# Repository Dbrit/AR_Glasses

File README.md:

# The HUDset
EE445L AR glasses final project

https://www.youtube.com/watch?v=10rfZ0_9bQ0

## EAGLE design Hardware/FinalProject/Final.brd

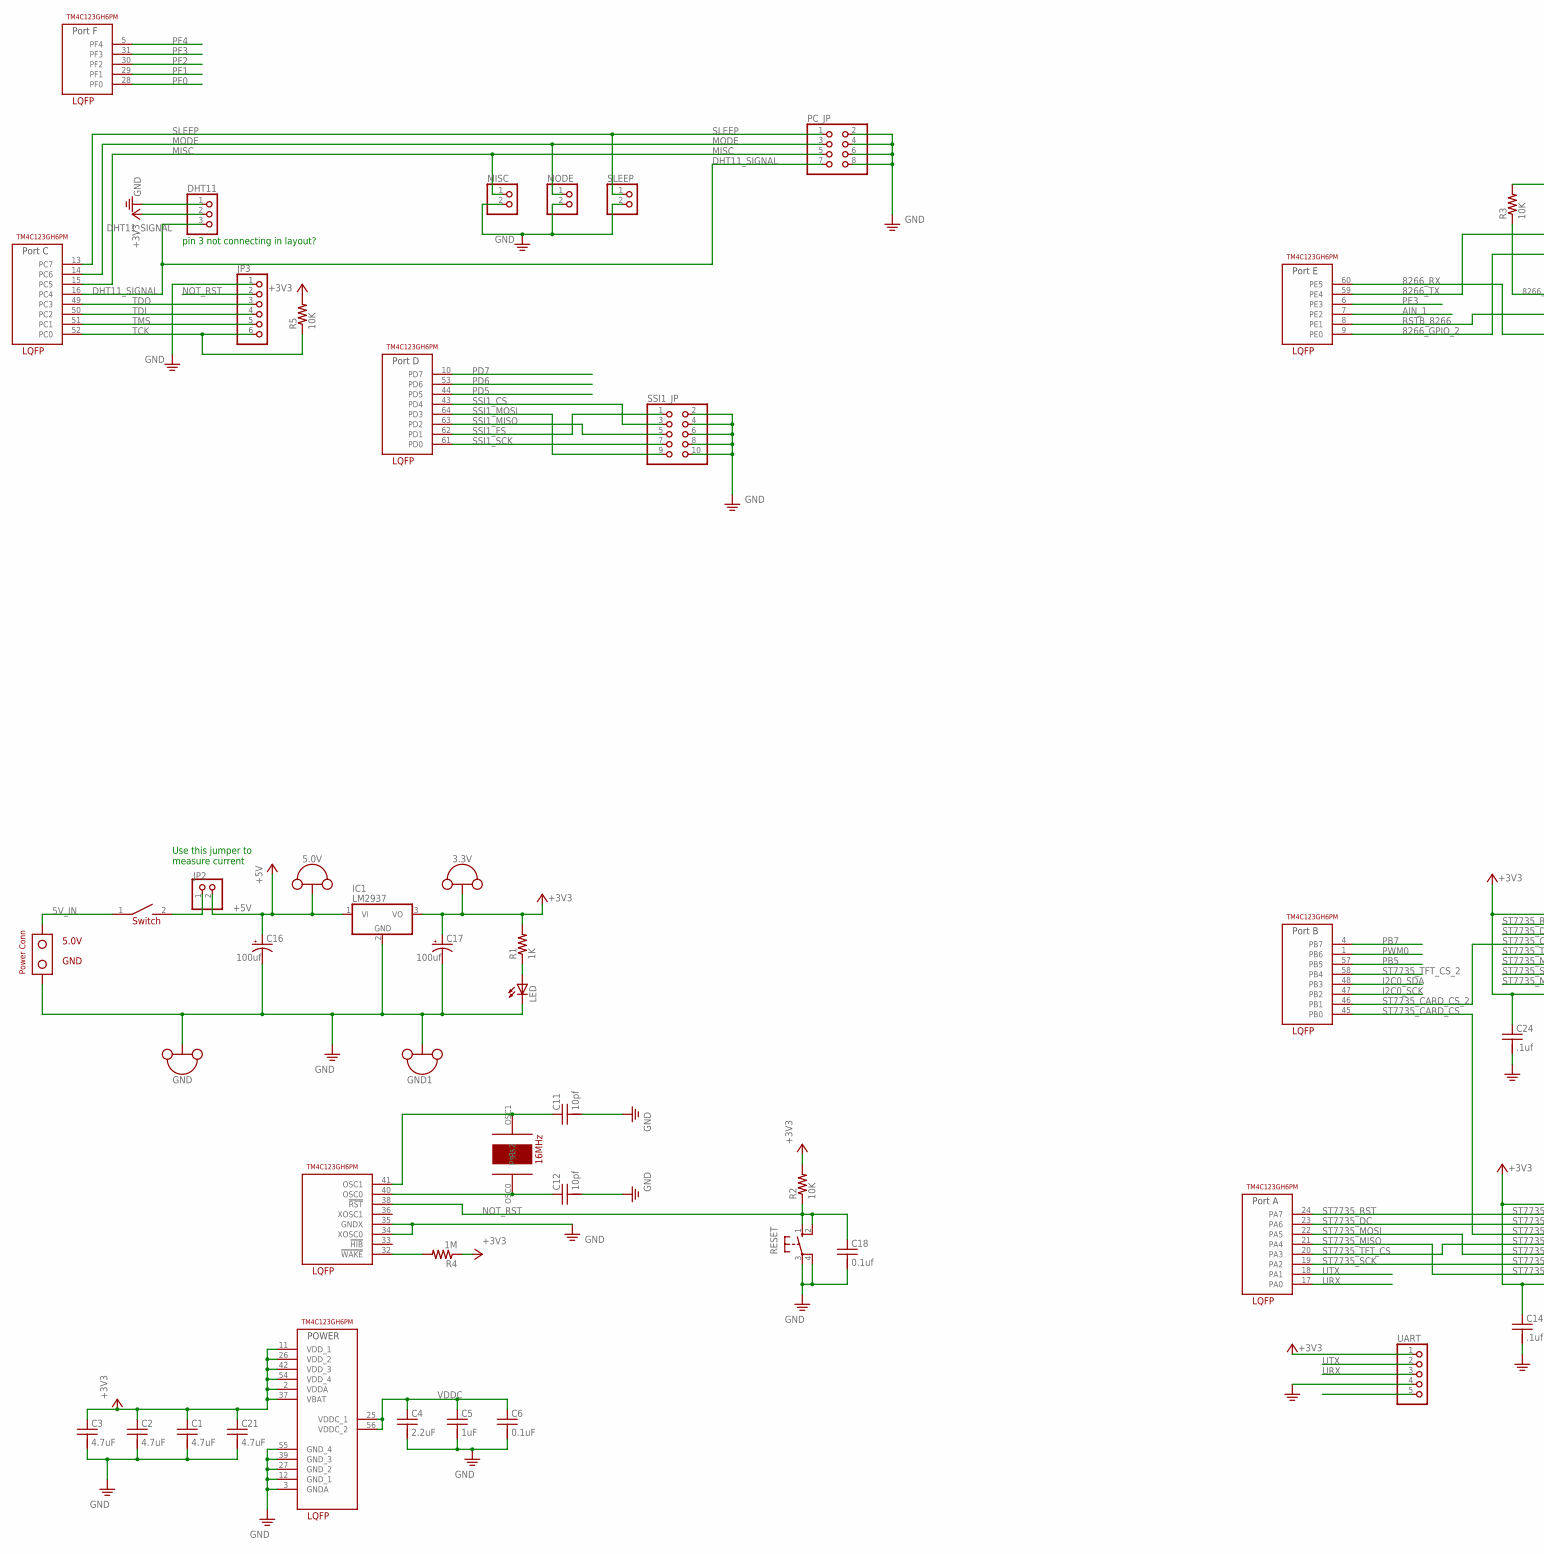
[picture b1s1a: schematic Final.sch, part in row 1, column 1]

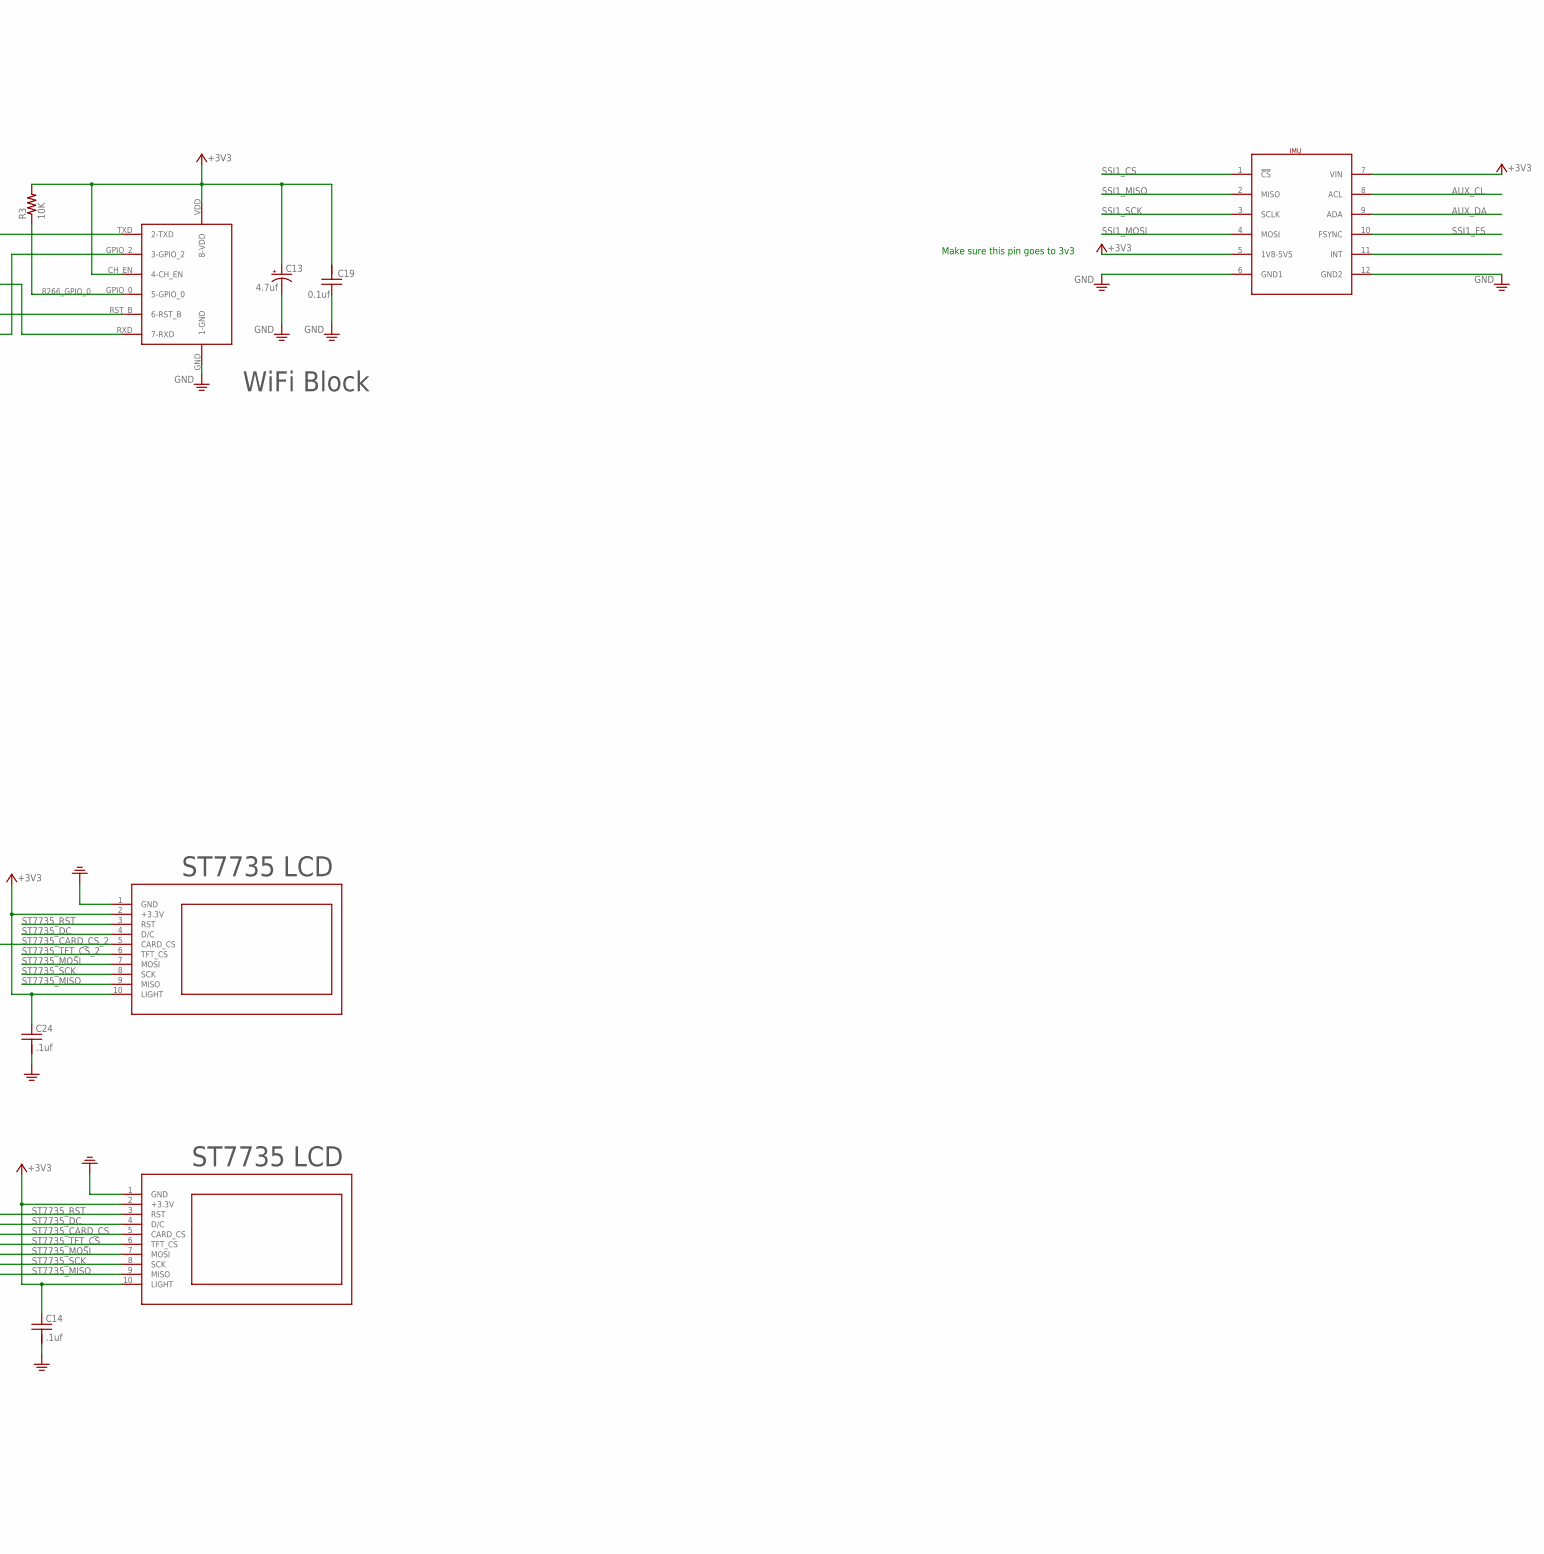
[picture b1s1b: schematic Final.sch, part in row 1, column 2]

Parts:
3.3V, 5.0V: TP_LOOP
C1, C2, C3, C21: 4.7uF; C0603K
C4: 2.2uF; C0603K
C5: 1uF; C0603K
C6: 0.1uF; C0603K
C11, C12: 10pf; CAP100MIL
C13: 4.7uf; CAP200MILPOLARIZED
C14, C24: .1uf; CAP200MIL
C16, C17: 100uf; CAP200MILPOLARIZED
C18: 0.1uf; CAP100MIL
C19: 0.1uf; CAP200MIL
DHT11: PINHD-1X3; 1X03
GND, GND1: TP_LOOP
IC1: LM2937; TO220
IMU: SEN-15335
JP2: PINHD-1X2; 1X02
JP3: PINHD-1X6; 1X06
LED: LED5MM
MISC: PINHD-1X2; 1X02
MODE: PINHD-1X2; 1X02
PC_JP: PINHD-2X4; 2X04
POWER_SWITCH: SW_POWER_100MIL; SW_POWER
R1: 1K; RES200MIL
R2, R5: 10K; RES200MIL
R3: 10K; RES300MIL
R4: 1M; RES200MIL
RESET: B3F-1052; B3F-10XX
SLEEP: PINHD-1X2; 1X02
SSI1_JP: PINHD-2X5; 2X05
U$1: TM4C123GH6PM; QFP50P1200X1200X160-64N
U$2: 16MHZ_CRYSTAL
U$3: ESP_8266; ESP8266
U$4: POWER_CONN
U$5, U$6: ST7735
UART: PINHD-1X5; 1X05

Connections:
5V_IN: POWER_SWITCH.1, U$4.VDD
8266_GPIO_0: R3.1, U$3.GPIO_0 (5-GPIO_0)
8266_GPIO_2: U$1.9 (PE0), U$3.GPIO_2 (3-GPIO_2)
8266_RX: U$1.60 (PE5), U$3.RXD (7-RXD)
8266_TX: U$1.59 (PE4), U$3.TXD (2-TXD)
+3V3: 3.3V.P$1, 3.3V.P$2, C1.1, C2.1, C3.1, C13.+, C14.1, C17.+, C19.2, C21.1, C24.1, DHT11.2, IC1.3 (VO), IMU.5 (1V8-5V5), IMU.7 (VIN), R1.2, R2.2, R3.2, R4.1, R5.2, U$1.2 (VDDA), U$1.11 (VDD_1), U$1.26 (VDD_2), U$1.37 (VBAT), U$1.42 (VDD_3), U$1.54 (VDD_4), U$3.CH_EN (4-CH_EN), U$3.VDD (8-VDD), U$5.2 (+3.3V), U$5.10 (LIGHT), U$6.2 (+3.3V), U$6.10 (LIGHT), UART.1
+5V: 5.0V.P$1, 5.0V.P$2, C16.+, IC1.1 (VI), JP2.2
AIN_1: U$1.7 (PE2)
AUX_CL: IMU.8 (ACL)
AUX_DA: IMU.9 (ADA)
CURRENT_1: JP2.1, POWER_SWITCH.2
DHT11_SIGNAL: DHT11.3, PC_JP.7, U$1.16 (PC4)
GND: C1.2, C2.2, C3.2, C4.2, C5.2, C6.2, C11.2, C12.2, C13.-, C14.2, C16.-, C17.-, C18.2, C19.1, C21.2, C24.2, DHT11.1, GND.P$1, GND.P$2, GND1.P$1, GND1.P$2, IC1.2 (GND), IMU.6 (GND1), IMU.12 (GND2), JP3.1, LED.K (C), MISC.2, MODE.2, PC_JP.2, PC_JP.4, PC_JP.6, PC_JP.8, RESET.3, RESET.4 (P1), SLEEP.2, SSI1_JP.2, SSI1_JP.4, SSI1_JP.6, SSI1_JP.8, SSI1_JP.10, U$1.3 (GNDA), U$1.12 (GND_1), U$1.27 (GND_2), U$1.34 (XOSC0), U$1.35 (GNDX), U$1.39 (GND_3), U$1.55 (GND_4), U$3.GND (1-GND), U$4.GND, U$5.1 (GND), U$6.1 (GND), UART.4
I2C0_SCK: U$1.47 (PB2)
I2C0_SDA: U$1.48 (PB3)
LED_CATHODE: LED.A, R1.1
MISC: MISC.1, PC_JP.5, U$1.15 (PC5)
MODE: MODE.1, PC_JP.3, U$1.14 (PC6)
NOT_RST: C18.1, JP3.2, R2.1, RESET.1 (S), RESET.2 (S1), U$1.38 (!RST)
NOT_WAKE: R4.2, U$1.32 (!WAKE)
OSC0: C12.1, U$1.40 (OSC0), U$2.OSC0
OSC1: C11.1, U$1.41 (OSC1), U$2.OSC1
PB5: U$1.57 (PB5)
PB7: U$1.4 (PB7)
PD5: U$1.44 (PD5)
PD6: U$1.53 (PD6)
PD7: U$1.10 (PD7)
PE3: U$1.6 (PE3)
PF0: U$1.28 (PF0)
PF1: U$1.29 (PF1)
PF2: U$1.30 (PF2)
PF3: U$1.31 (PF3)
PF4: U$1.5 (PF4)
PWM0: U$1.1 (PB6)
RSTB_8266: U$1.8 (PE1), U$3.RST_B (6-RST_B)
SLEEP: PC_JP.1, SLEEP.1, U$1.13 (PC7)
SSI1_CS: IMU.1 (!CS), SSI1_JP.3, U$1.43 (PD4)
SSI1_FS: IMU.10 (FSYNC), SSI1_JP.1, U$1.62 (PD1)
SSI1_MISO: IMU.2 (MISO), SSI1_JP.5, U$1.63 (PD2)
SSI1_MOSI: IMU.4 (MOSI), SSI1_JP.9, U$1.64 (PD3)
SSI1_SCK: IMU.3 (SCLK), SSI1_JP.7, U$1.61 (PD0)
ST7735_CARD_CS: U$1.45 (PB0), U$5.5 (CARD_CS)
ST7735_CARD_CS_2: U$1.46 (PB1), U$6.5 (CARD_CS)
ST7735_DC: U$1.23 (PA6), U$5.4 (D/C), U$6.4 (D/C)
ST7735_MISO: U$1.21 (PA4), U$5.9 (MISO), U$6.9 (MISO)
ST7735_MOSI: U$1.22 (PA5), U$5.7 (MOSI), U$6.7 (MOSI)
ST7735_RST: U$1.24 (PA7), U$5.3 (RST), U$6.3 (RST)
ST7735_SCK: U$1.19 (PA2), U$5.8 (SCK), U$6.8 (SCK)
ST7735_TFT_CS: U$1.20 (PA3), U$5.6 (TFT_CS)
ST7735_TFT_CS_2: U$1.58 (PB4), U$6.6 (TFT_CS)
TCK: JP3.6, R5.1, U$1.52 (PC0)
TDI: JP3.4, U$1.50 (PC2)
TDO: JP3.3, U$1.49 (PC3)
TMS: JP3.5, U$1.51 (PC1)
URX: U$1.17 (PA0), UART.3
UTX: U$1.18 (PA1), UART.2
VDDC: C4.1, C5.1, C6.1, U$1.25 (VDDC_1), U$1.56 (VDDC_2)

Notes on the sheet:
WiFi Block
ST7735 LCD
Use this jumper to measure current
pin 3 not connecting in layout?
Make sure this pin goes to 3v3

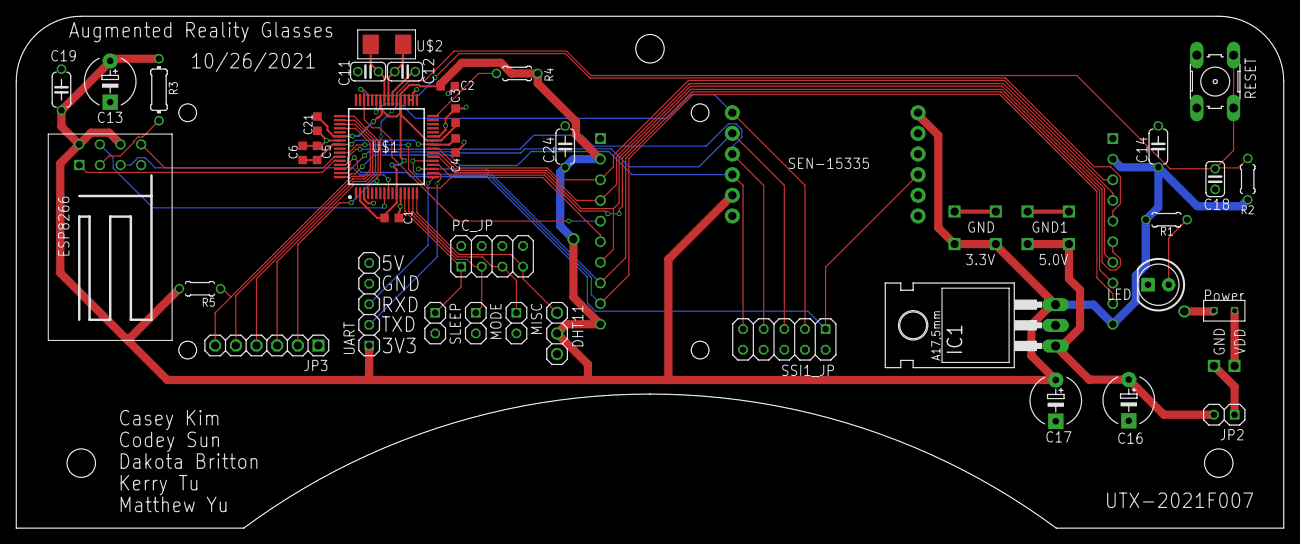
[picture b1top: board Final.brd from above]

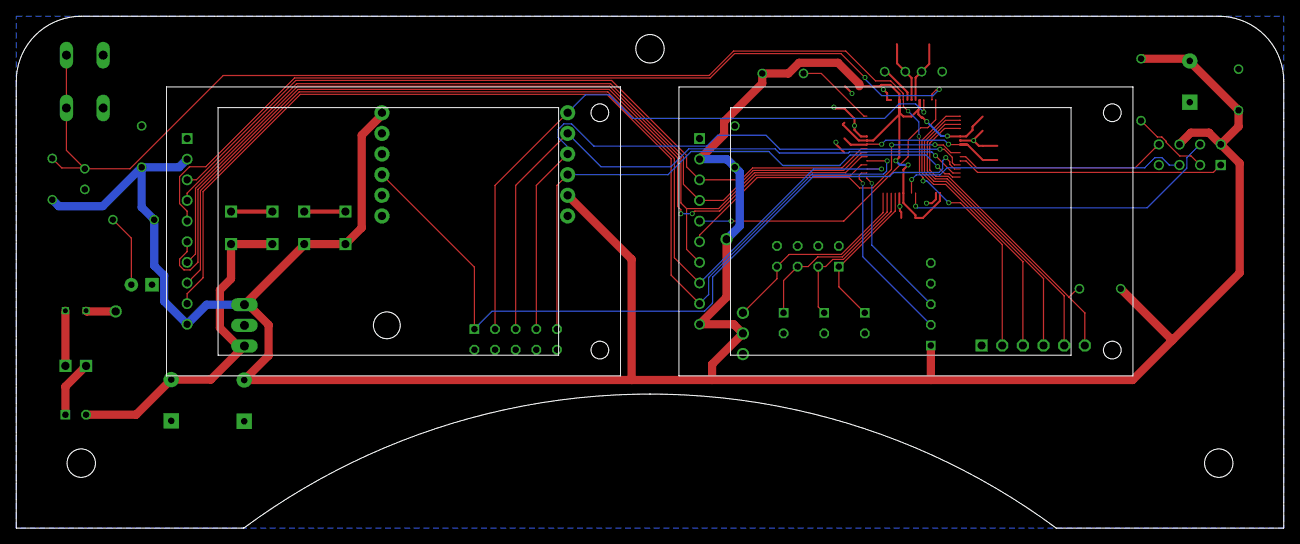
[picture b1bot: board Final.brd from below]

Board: 2 copper layers, 156.0 x 63.0 mm, 45 parts (2 on the bottom side), 40 nets.

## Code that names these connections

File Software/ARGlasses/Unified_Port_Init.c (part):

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// Port A drives the ST7735 LCD 
//
// Backlight (pin 10) connected to +3.3 V
// MISO      (pin 9)  connected to PA4
// SCK       (pin 8)  connected to PA2 (SSI0Clk)
// MOSI      (pin 7)  connected to PA5 (SSI0Tx)
// TFT_CS    (pin 6)  connected to PA3 (SSI0Fss)
// CARD_CS   (pin 5)  connected to PB0 (GPIO)
// Data/CMD  (pin 4)  connected to PA6 (GPIO), high for data, low for command
// RESET     (pin 3)  connected to PA7 (GPIO)
// VCC       (pin 2)  connected to +3.3 V
// Gnd       (pin 1)  connected to ground
//
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  SYSCTL_RCGCGPIO_R     |= 0x01;            // Activate port A
  while((SYSCTL_PRGPIO_R & 0x01)==0){};     // allow time for clock to start
    
  GPIO_PORTA_DIR_R      |= 0xC8;            // make PA3,6,7 out
  GPIO_PORTA_AFSEL_R    &= ~0xC8;           // disable alt funct on PA3,6,7
  GPIO_PORTA_DEN_R      |= 0xC8;            // enable digital I/O on PA3,6,7
  
  // configure PA3,6,7 as GPIO
  GPIO_PORTA_PCTL_R      = (GPIO_PORTA_PCTL_R
                         & 0x00FF0FFF)
                         + 0x00000000;
  
  GPIO_PORTA_AMSEL_R    &= ~0xC8;           // disable analog functionality on PA3,6,7

  // initialize SSI0
  GPIO_PORTA_AFSEL_R    |= 0x2C;            // enable alt funct on PA2,3,5
  GPIO_PORTA_DEN_R      |= 0x2C;            // enable digital I/O on PA2,3,5
 
  // configure PA2,3,5 as SSI
  GPIO_PORTA_PCTL_R      = (GPIO_PORTA_PCTL_R
                         & 0xFF0F00FF)
                         + 0x00202200;
  
  GPIO_PORTA_AMSEL_R    &= ~0x2C;           // disable analog functionality on PA2,3,5
  SSI0_CR1_R            &= ~SSI_CR1_SSE;    // disable SSI
  SSI0_CR1_R            &= ~SSI_CR1_MS;     // master mode
  
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// PB7 = PWM Ouptut to JP6 (M0PWM1)
// PB6 = PWM Output to Motor (M0PWM0)
// PB5 = ADC Input (AIN11)
// PB4 = Timer Capture input (T1CCP0)
// PB3 = GPIO 
// PB2 = GPIO/I2C0
// PB1 = GPIO/I2C0CL
// PB0 = ST7735 Card CS

void Port_B_Init(void){ 
  
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  GPIO_PORTB_DEN_R      &= ~0x20;           // disable digital I/O on PB5
  GPIO_PORTB_AMSEL_R    |=  0x20;           // enable analog functionality on PB5

  // ----------------- Initialize PB4 as Timer Capture input (T1CCP0) ---------
  GPIO_PORTB_DIR_R      &= ~0x10;           // make PB4 input
  GPIO_PORTB_AFSEL_R    |= 0x10;            // enable alt funct on PB4
  GPIO_PORTB_DEN_R      |= 0x10;            // enable digital I/O on PB4
                                            // configure PB4 (T1CCP0)
  GPIO_PORTB_PCTL_R     = (GPIO_PORTB_PCTL_R 
                        &  0xFFF0FFFF)
                        +  0x00070000;
  GPIO_PORTB_AMSEL_R    &= ~0x10;           // disable analog functionality on PB4

  // ----------------- Initialize PB3-0 as GPIO ---------
                                      
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// ----------------    PORT C Initialization   --------------------------------
// ----------------------------------------------------------------------------
//
// PC4 = UP switch
// PC5 = RIGHT switch
// PC6 = LEFT switch
// PC7 = DOWN switch
//

void Port_C_Init(void){ 
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   
  GPIO_PORTC_PCTL_R     &= ~0xFFFF0000;   // regular GPIO
  GPIO_PORTC_AMSEL_R    &= ~0xF0;         // disable analog function 
  GPIO_PORTC_DIR_R      &= ~0xF0;         // inputs on PC7-PC4
  GPIO_PORTC_AFSEL_R    &= ~0xF0;         // regular port function
  GPIO_PORTC_PUR_R       =  0xF0;         // enable pull-up on PC7-PC4
  GPIO_PORTC_DEN_R      |=  0xF0;         // enable digital port 
  }  
  
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//
// PD7 = U2TX
// PD6 = U2RX
// PD3 = SSI1_MOSI  (to TLV5616)
// PD2 = AIN5 (Monitor DAC_OUT signal from TLV5616)
// PD1 = SSI1_FS/CS (to TLV5616)
// PD0 = SSI1_SCK   (to TLV5616)
  
void Port_D_Init(void){
 
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                         & 0x00FFFFFF)
                         | 0x11000000;      // configure PD6, PD7 as UART
 
   // ---------------  Initialize PD2 as AIN5  ----------------------------------  
   
  GPIO_PORTD_DIR_R      &= ~0x04;           // make PD2 input
  GPIO_PORTD_AFSEL_R    |=  0x04;           // enable alternate function on PD2
  GPIO_PORTD_DEN_R      &= ~0x04;           // disable digital I/O on PD2
  GPIO_PORTD_AMSEL_R    |=  0x04;           // enable analog functionality on PD2

  // ---------------  Initialize PD3,1,0 as SSI1 MOSI, FS & SCK  ---------------- 
    
  GPIO_PORTD_AMSEL_R    &= ~0x0B;           // disable analog functionality on PD
  GPIO_PORTD_AFSEL_R    |=  0x0B;           // enable alt funct on PD3,1,0
  GPIO_PORTD_DEN_R      |=  0x0B;           // enable digital I/O on PD3,1,0
  GPIO_PORTD_PCTL_R      = (GPIO_PORTD_PCTL_R
                          & 0xFFFF0F00)
                          + 0x00002022;
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// ----------------    PORT E Initialization   --------------------------------
// ----------------------------------------------------------------------------
//
// PE5 = U5TX
// PE4 = U5RX
// PE3 = Heartbeat LED
// PE2 = AIN_1 (DAC_OUT Monitor)
// PE1 = RSTB_8266
// PE0 = 8266_ GPIO_2 

void Port_E_Init(void){

  SYSCTL_RCGCGPIO_R     |= 0x10;            // activate port E
  while((SYSCTL_PRGPIO_R & 0x10)==0){};

 // ---------------  Initialize PE5 as U5TX, PE4 as U5RX  -----------------------  

  GPIO_PORTE_AFSEL_R    |= 0x30;            // enable alt funct on PE5-4
  GPIO_PORTE_DEN_R      |= 0x30;            // enable digital I/O on PE5-4
                                            // configure PE5-4 as UART
  GPIO_PORTE_PCTL_R      = (GPIO_PORTE_PCTL_R
                         & 0xFF00FFFF)
                         + 0x00110000;
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 // ---------------  Initialize PE3,1,0 as GPIO  ---------------------------------  

  GPIO_PORTE_DIR_R      |=  0x0A;           // output digital I/O on PE3,1
  GPIO_PORTE_DIR_R      &= ~0x01;           // input digital I/O on PE0
  GPIO_PORTE_AMSEL_R    &= ~0x0B;           // disable analog functionality on PE3,1,0
  GPIO_PORTE_AFSEL_R    &= ~0x0B;           // disable alt funct on PE3,1,0
  GPIO_PORTE_DEN_R      |=  0x0B;           // enable digital I/O on PE3,1,0
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
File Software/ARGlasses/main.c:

// filename ******** main.c ************** 
// Lisong Sun, Kerry Tu, Dakota Britton, Casey Kim
// Created: October 26, 2021
// C file with main functions for the HUDset.
// Lab 11
// TA: Matthew Yu
// Last edited: November 25, 2021

// ST7735 Connections
// Backlight (pin 10) connected to +3.3 V
// MISO (pin 9) unconnected 
// SCK (pin 8) connected to PA2 (SSI0Clk)
// MOSI (pin 7) connected to PA5 (SSI0Tx)
// TFT_CS (pin 6) connected to PA3 (SSI0Fss)
// TFT_CS2 connected to PB4
// CARD_CS (pin 5) unconnected
// Data/Command (pin 4) connected to PA6 (GPIO)
// RESET (pin 3) connected to PA7 (GPIO)
// VCC (pin 2) connected to +3.3 V
// Gnd (pin 1) connected to ground

// Port C Connections
// PC4 connected to DHT11 signal
// PC5 connected to the button
// PC6 connected to the flashlight LED

// ESP8266 Connections
// PE0 to 8266_GPIO2
// PE1 to 8266_Reset
// PE4 to 8266_TX
// PE5 to 8266_RX

// ICM20948 Connections
// PD0 to SSI1_SCK
// PD1 to SSI1_FS
// PD2 to SSI1_MISO
// PD3 to SSI1_MOSI
// PD4 to SSI1_CS

//#include <stdio.h>
#include <stdint.h>
//#include "string.h"
#include "../inc/PLL.h"
#include "../inc/tm4c123gh6pm.h"
#include "../inc/LaunchPad.h"
#include "../inc/CortexM.h"
#include "Buttons.h"
#include "Clock.h"
#include "DHT11.h"
#include "esp8266.h"
#include "APICaller.h"
#include "ICM20948.h"
#include "../inc/Unified_Port_Init.h"
#include "tests.h"

// semaphores for button inputs
volatile uint8_t press_flag;

// current menu global
enum MenuMode currentMenu;

// Initialize the next menu
void ChangeMenu(void) {
	switch (currentMenu) {
		case TimeMode: {
			Clock_ShowTimeMenu();
		} break;
		case WeatherMode: {
			Clock_ShowWeatherMenu();
		} break;
		case TempMode: {
			Clock_ShowTempMenu();
		} break;
		case CompassMode: {
			Clock_ShowCompassMenu();
		} break;
		case BlankMode:{
			Clock_ShowBlankMenu();
		} break;
		case LightMode:{
			Clock_ShowLightMenu();
		} break;
		default:
			break;
	}
}

// Display startup animation
void Welcome_Screen(void) {
	ST7735_FillScreen(ST7735_BLACK);
	for (int i = 0; i <= 31; i++) {
		uint16_t color = (i<<11)+(i<<6)+i;
		ST7735_SetTextColor(color); 
		ST7735_SetCursor(4,5);
		ST7735_OutString("Welcome to HUD");
		SysTick80_Wait10ms(3);
	}
	
	SysTick80_Wait10ms(150);
	
	for (int i = 31; i >= 0; i--) {
		uint16_t color = (i<<11)+(i<<6)+i;
		ST7735_SetTextColor(color); 
		ST7735_SetCursor(4,5);
		ST7735_OutString("Welcome to HUD");
		SysTick80_Wait10ms(3);
	}
	
	ST7735_SetTextColor(ST7735_WHITE);
	SysTick80_Wait10ms(100);
}
// Initialize the ST7735 + chip selects
void LCD_Init(void) {
	// startup LCDs
	Port_B_Init(); // chip select
  ST7735_InitR(INITR_REDTAB);
	PA3_Init();    // chip select
	ST7735_SetBGColor(ST7735_BLACK);
	ST7735_SetTextColor(ST7735_WHITE);
	ST7735_SetRotation(3);
	ST7735_FillScreen(ST7735_BLACK);
}

int main(void){
	// Initialization
  PLL_Init(Bus80MHz); 
	DisableInterrupts();
	SysTick_Init();
	// Bootup
	LCD_Init();
	//Test_LCD();
	//Test_Image();
	
	Buttons_Init();
	
	ST7735_SetCursor(7,2);
	ST7735_OutString("Init DHT...");
	DHT11_Init();
	ST7735_OutString("S");
	//Test_DHT11();
	ICM_Boot();
	//Test_ICM20948();
	ST7735_SetCursor(7,5);
	ST7735_OutString("Init ESP...");
	APICaller_Init();
	//Test_API();
	ST7735_OutString("S");
	Clock_Init();
	ST7735_SetCursor(7,6);
	ST7735_OutString("Starting up!");
	Welcome_Screen();
	
	EnableInterrupts();
	ChangeMenu();
	
	// Main logic
  while(1){

		uint8_t press = press_flag;
		press_flag = 0;
		uint8_t menu = press;
		
		if (menu == 1) {
			press_flag = 0;
			
			if(currentMenu == BlankMode){
				currentMenu = TimeMode;
			}
			else{
				currentMenu = (currentMenu + 1);
			}
			ChangeMenu();
		}
		
		switch (currentMenu) {
			case TimeMode: {
				Clock_UpdateTimeMenu();
			} break;
			case WeatherMode: {
				Clock_UpdateWeatherMenu();
			} break;
			case TempMode: {
				Clock_UpdateTempMenu();
			} break;
			case CompassMode: {
				Clock_UpdateCompassMenu();
			} break;
			case BlankMode:{
				Clock_UpdateBlankMenu();
			} break;
			case LightMode:{
				Clock_UpdateLightMenu();
			} break;
			default:
				break;
		}
		
  }
} 

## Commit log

2021-10-28 Changed to SMD caps near TM4C
2021-10-28 Add lib and fixed cap placement
2021-11-02 WIP ESP8266 functions using AT commands
    First prototype for AT commands for ESP8266 to call OpenWeather API. Currently is not functioning correctly; may need a different solution than using ESP8266_Outstring function
2021-11-25 Completed HUDset code
2021-11-26 3d printed parts
2021-11-28 calibrated IMU
2021-11-28 fixed fahrenheit conversion
